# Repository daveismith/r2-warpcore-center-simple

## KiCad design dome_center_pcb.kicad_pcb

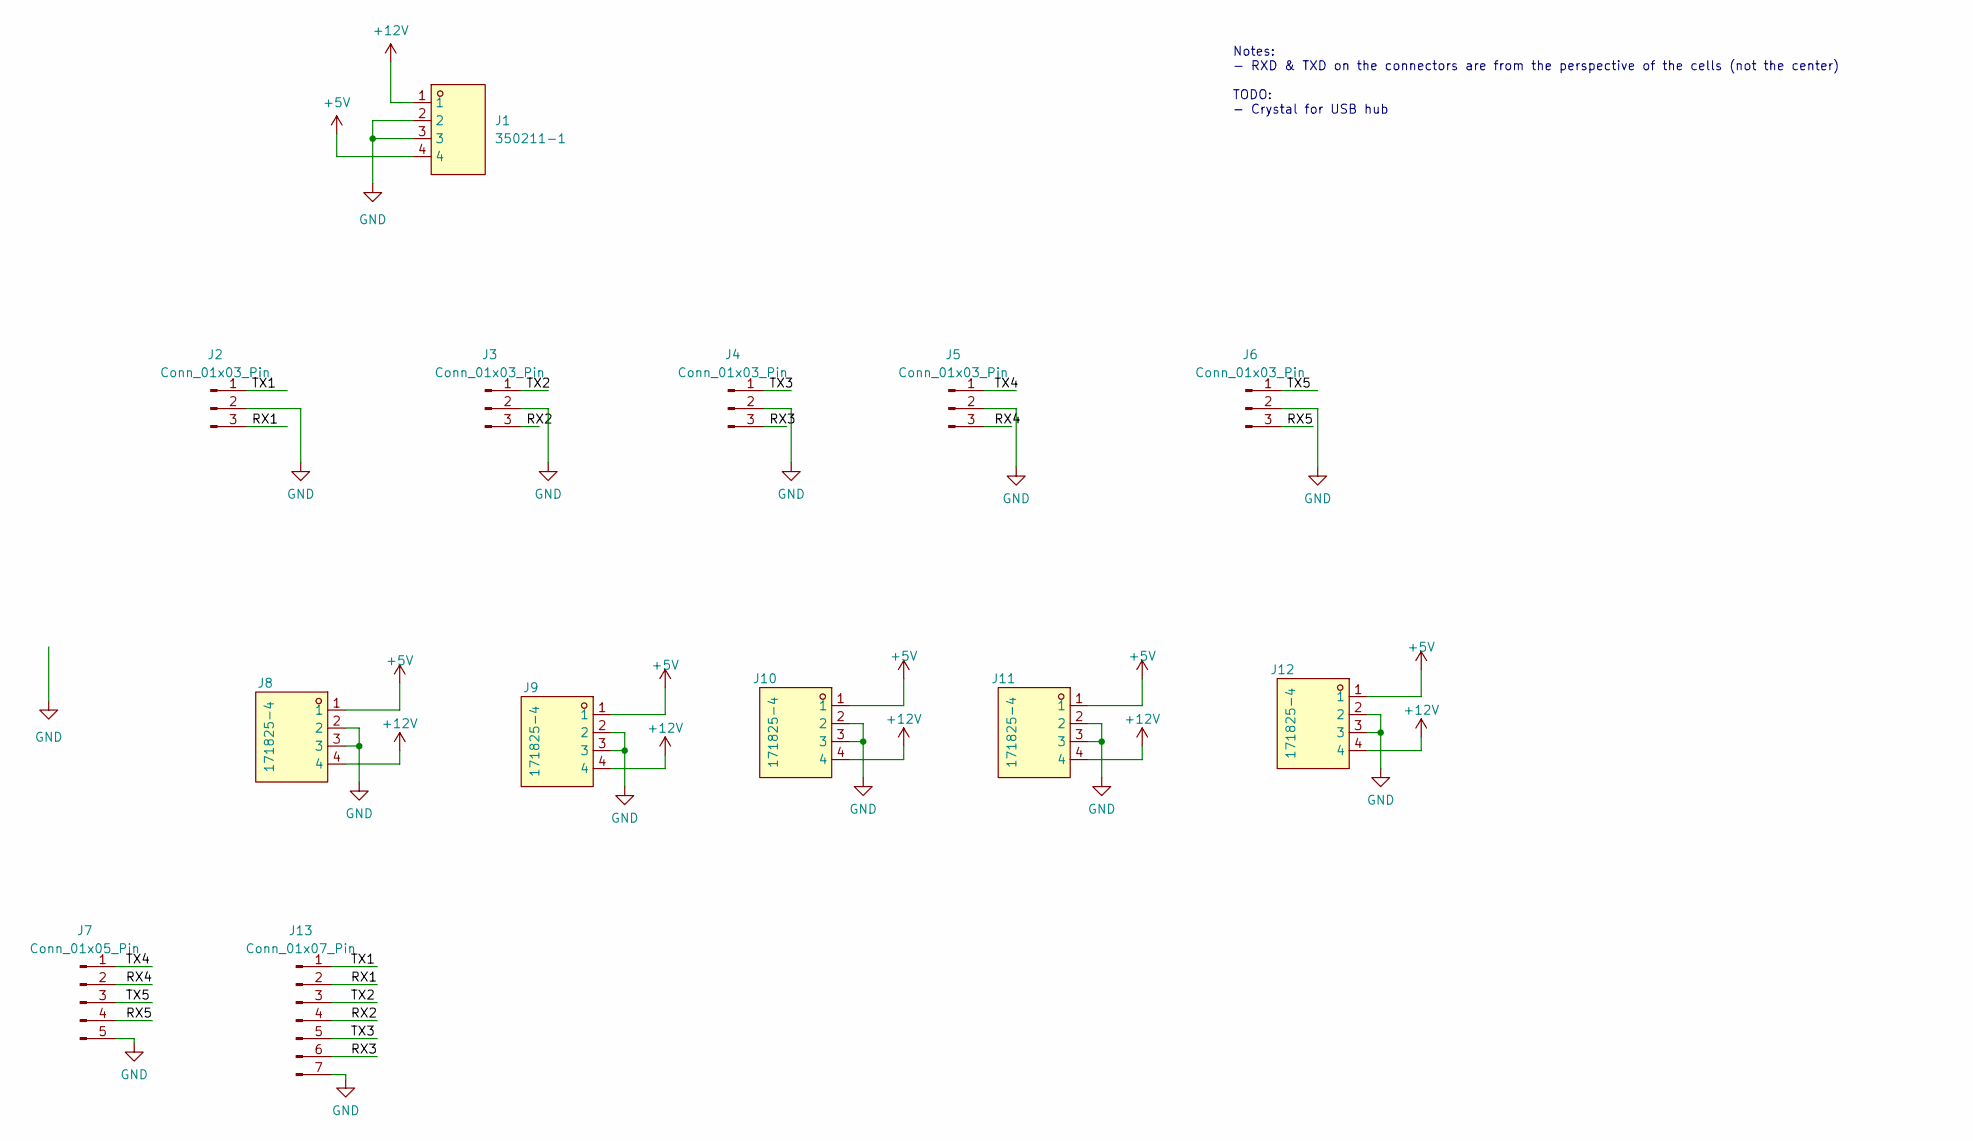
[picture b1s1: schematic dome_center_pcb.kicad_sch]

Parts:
J1: 350211-1; CONN-TH_350211-1; LCSC Part C305826
J2, J3, J4, J5, J6: Conn_01x03_Pin; JST_XH_B3B-XH-A_1x03_P2.50mm_Vertical
J7: Conn_01x05_Pin; JST_XH_B5B-XH-A_1x05_P2.50mm_Vertical
J8, J9, J10, J11, J12: 171825-4; HDR-TH_4P-P2.54-D1.0; LCSC Part C210162
J13: Conn_01x07_Pin; JST_XH_B7B-XH-A_1x07_P2.50mm_Vertical

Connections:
+5V: J1.4, J8.1, J9.1, J10.1, J11.1, J12.1
+12V: J1.1, J8.4, J9.4, J10.4, J11.4, J12.4
/RX1: J2.3, J13.2
/RX2: J3.3, J13.4
/RX3: J4.3, J13.6
/RX4: J5.3, J7.2
/RX5: J6.3, J7.4
/TX1: J2.1, J13.1
/TX2: J3.1, J13.3
/TX3: J4.1, J13.5
/TX4: J5.1, J7.1
/TX5: J6.1, J7.3
GND: J1.2, J1.3, J2.2, J3.2, J4.2, J5.2, J6.2, J7.5, J8.2, J8.3, J9.2, J9.3, J10.2, J10.3, J11.2, J11.3, J12.2, J12.3, J13.7

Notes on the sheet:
Notes: - RXD & TXD on the connectors are from the perspective of the cells (not the center) TODO: - Crystal for USB hub

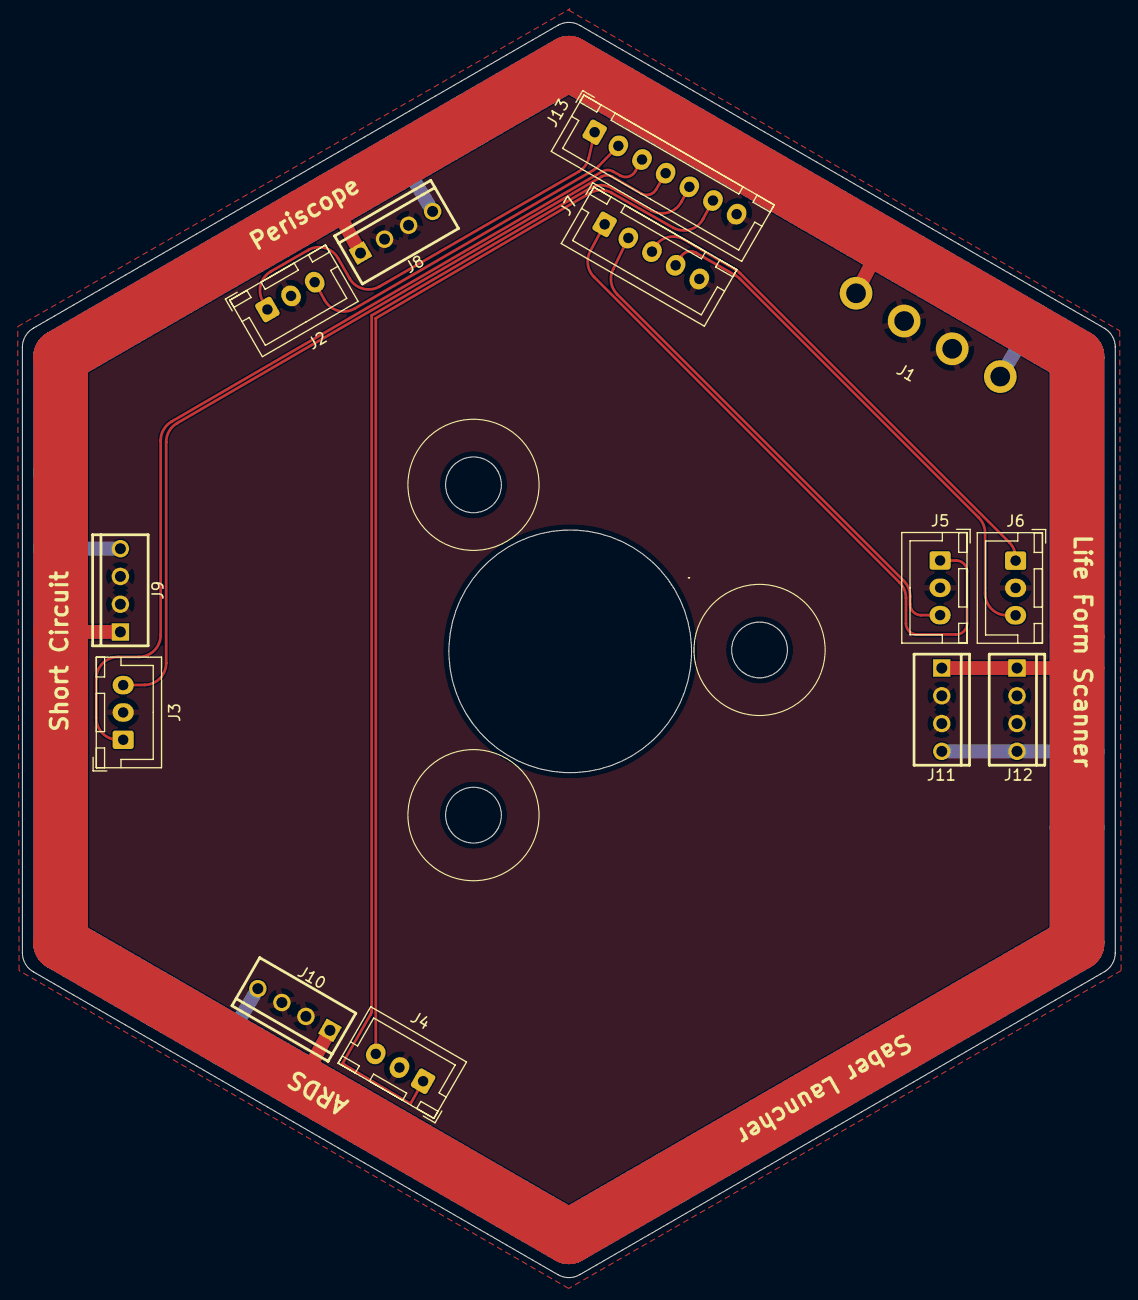
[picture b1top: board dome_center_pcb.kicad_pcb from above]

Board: 2 copper layers, 100.0 x 114.9 mm, 13 parts (0 on the bottom side), 13 nets.

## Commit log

2024-02-26 Initial Commit of Center Warp Core
2024-02-26 Updating XML
2024-02-26 Update the FTDI sheet reference to be lowercase like the file is in source control.
2024-03-24 Conversion to a simplified version.
